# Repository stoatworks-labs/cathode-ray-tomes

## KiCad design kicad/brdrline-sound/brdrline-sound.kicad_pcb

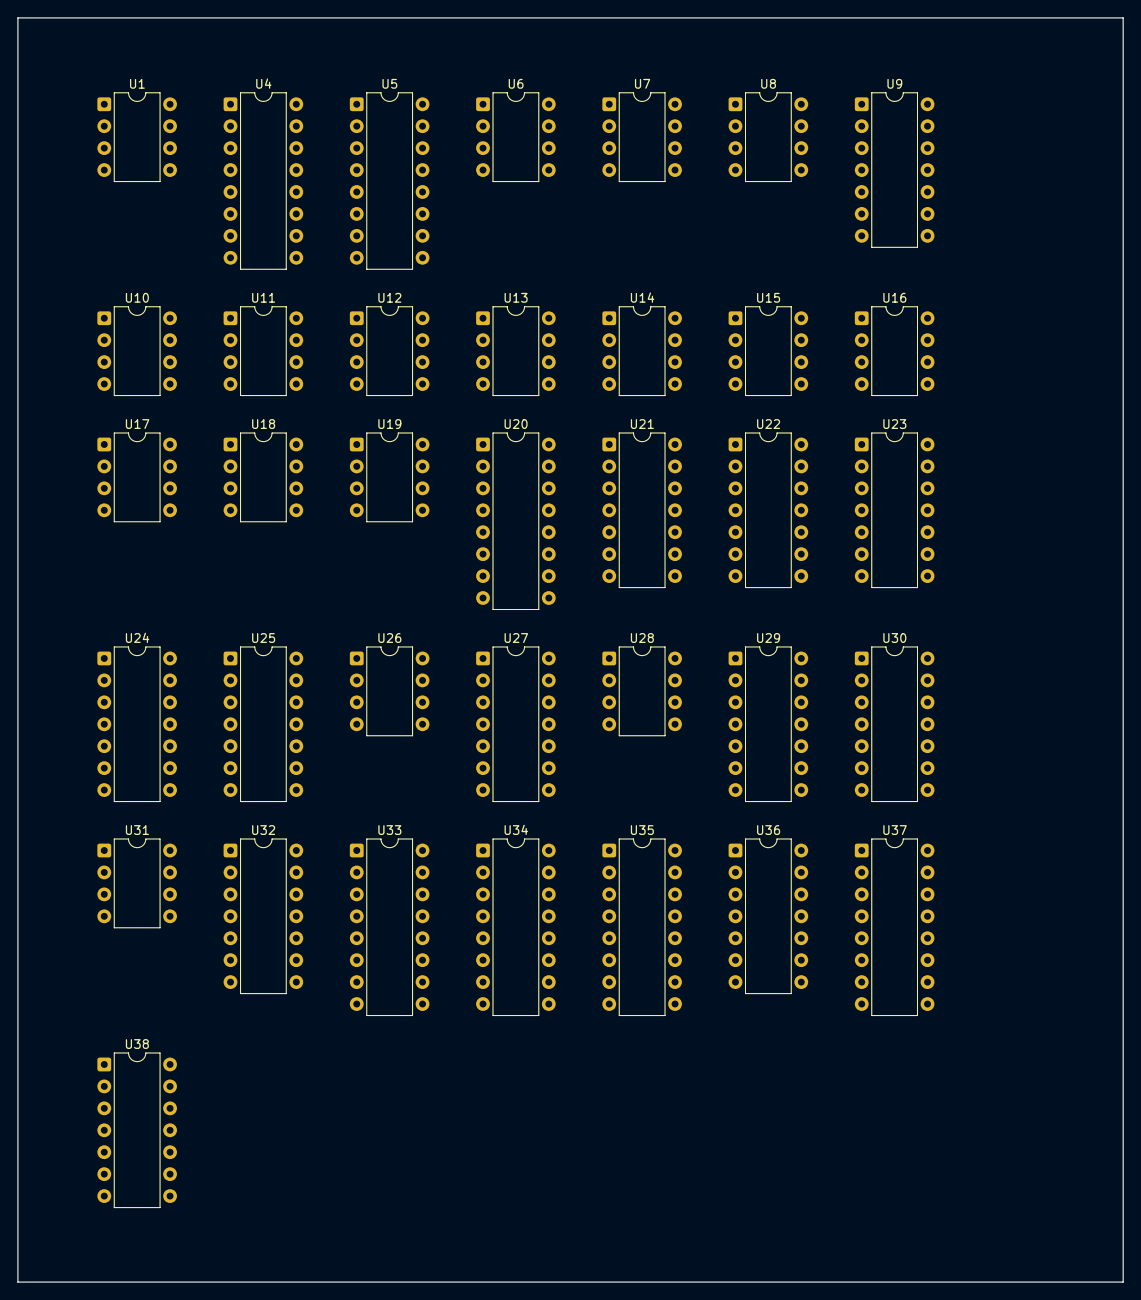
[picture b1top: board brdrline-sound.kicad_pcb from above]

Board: 2 copper layers, 128.0 x 146.4 mm, 36 parts (0 on the bottom side), 39 nets, no tracks yet.

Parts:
U1, U6, U7, U8, U10, U11, U12, U13, U14, U15, U16, U17, U18, U19, U28, U31: NE555; DIP-8_W7.62mm
U4, U5, U20: MB4391; DIP-16_W7.62mm
U9, U21, U22, U23, U24, U25, U27, U38: LM324; DIP-14_W7.62mm
U26: MM5837; DIP-8_W7.62mm
U29: 7408; DIP-14_W7.62mm
U30, U32: 7474; DIP-14_W7.62mm
U33, U34, U35, U37: 74123; DIP-16_W7.62mm
U36: 7416; DIP-14_W7.62mm

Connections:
+5V: U1.8, U4.12, U4.16, U5.12, U5.16, U6.8, U7.8, U8.8, U10.8, U11.8, U12.8, U13.8, U14.8, U15.8, U16.8, U17.8, U18.8, U19.8, U20.12, U20.16, U28.8, U29.14, U30.1, U30.4, U30.10, U30.13, U30.14, U31.8, U32.1, U32.4, U32.10, U32.13, U32.14, U33.2, U33.3, U33.10, U33.11, U33.16, U34.2, U34.3, U34.16, U35.2, U35.3, U35.10, U35.11, U35.16, U36.14, U37.2, U37.3, U37.10, U37.11, U37.16
+6V: U21.5, U27.3, U38.5
+12V: U9.4, U21.4, U22.4, U23.4, U24.4, U25.4, U26.4, U27.4, U38.4
ANIMAL_TRG: U34.1, U34.9
GND: U1.1, U4.3, U4.7, U5.3, U5.7, U6.1, U7.1, U8.1, U9.11, U10.1, U11.1, U12.1, U13.1, U14.1, U15.1, U16.1, U17.1, U18.1, U19.1, U20.3, U20.7, U21.11, U22.11, U23.11, U24.11, U25.11, U26.1, U26.2, U27.11, U28.1, U29.7, U30.7, U31.1, U32.7, U33.8, U34.8, U35.8, U36.7, U37.8, U37.9, U38.11
unnamed: U1.2, U1.6, U9.14
unnamed: U16.2, U16.6, U24.14
unnamed: U10.2, U10.6, U21.14
unnamed: U11.2, U11.6, U21.8
unnamed: U12.2, U12.6, U22.14
unnamed: U13.2, U13.6, U22.8
unnamed: U14.2, U14.6, U23.14
unnamed: U15.2, U15.6, U23.8
unnamed: U17.2, U17.6, U24.8
unnamed: U18.2, U18.6, U25.14
unnamed: U19.2, U19.6, U25.8
unnamed: U6.2, U6.6, U24.1
unnamed: U7.2, U7.6, U25.1
unnamed: U8.2, U8.6, U25.7
unnamed: U31.2, U31.6
unnamed: U28.6, U28.7
unnamed: U9.8, U9.9
unnamed: U18.5, U19.5
unnamed: U34.10, U34.11, U34.13
unnamed: U29.4, U30.8
unnamed: U31.4, U36.6
unnamed: U30.3, U30.11, U31.3, U32.3
unnamed: U32.2, U32.6, U32.11
unnamed: U32.8, U32.12
unnamed: U5.2, U38.13, U38.14
unnamed: U20.2, U27.13, U27.14
unnamed: U20.6, U21.1, U21.2
unnamed: U4.2, U22.6, U22.7
unnamed: U4.6, U23.1, U23.2
unnamed: U29.5, U30.6
unnamed: U29.6, U30.2
unnamed: U30.5, U30.12
unnamed: U5.6, U38.1, U38.2
RST: U1.4, U6.4, U7.4, U8.4, U10.4, U11.4, U12.4, U13.4, U14.4, U15.4, U16.4, U17.4, U18.4, U19.4, U37.12

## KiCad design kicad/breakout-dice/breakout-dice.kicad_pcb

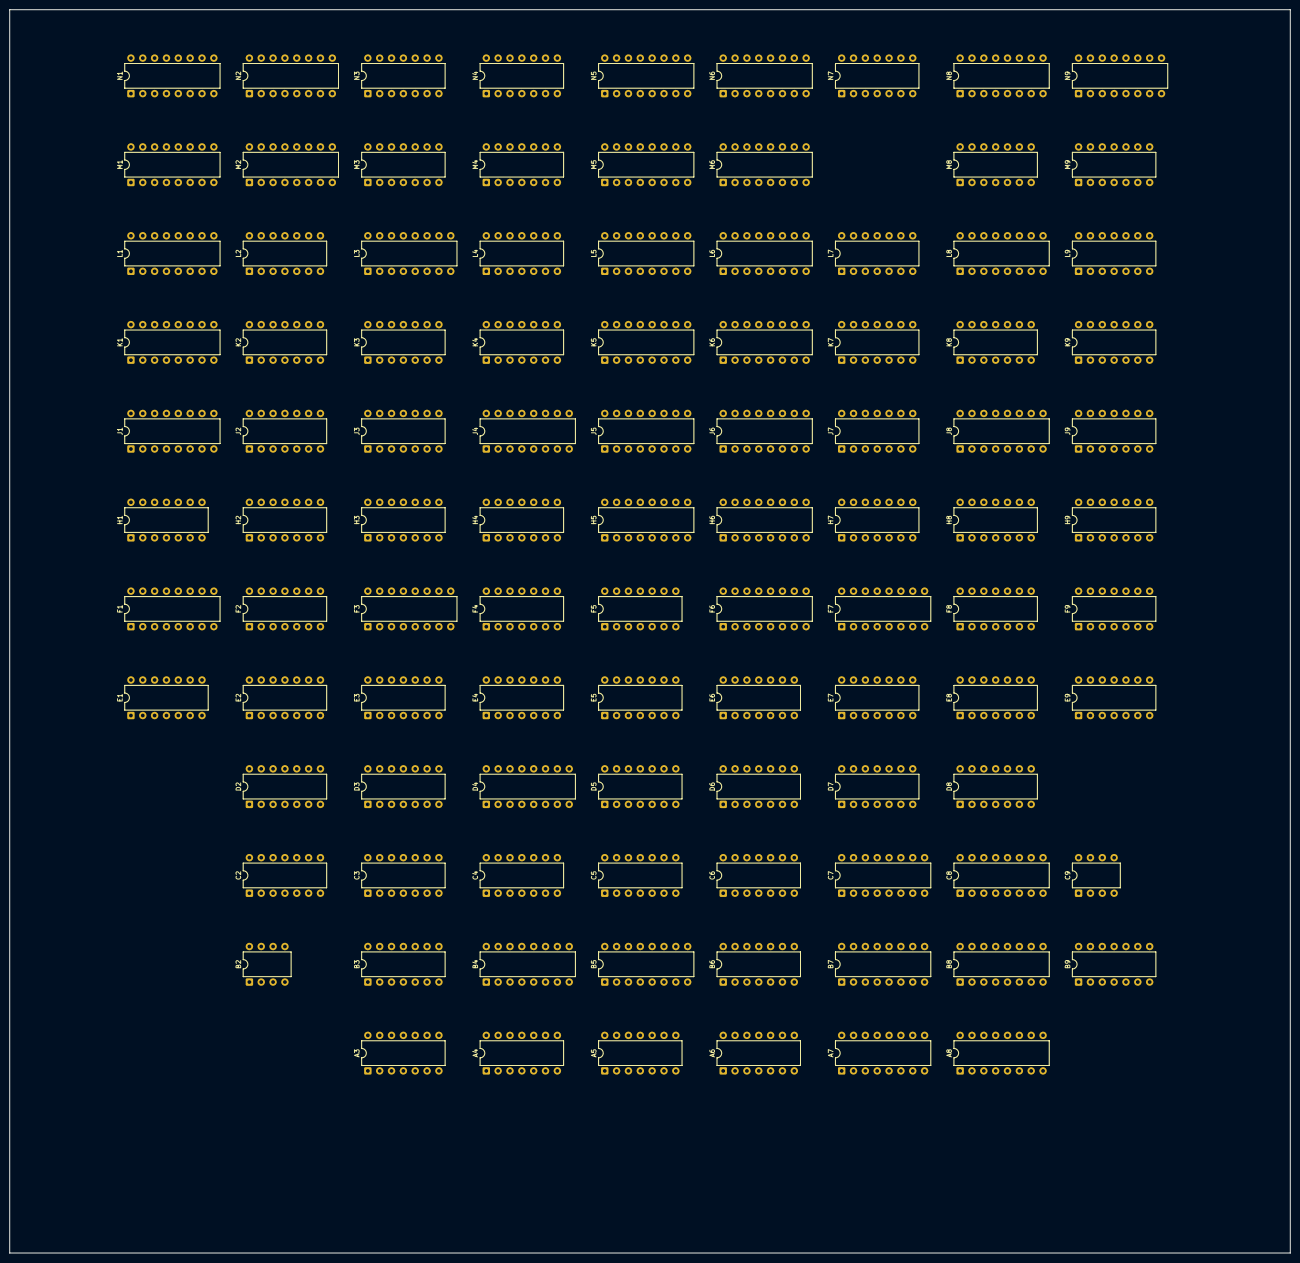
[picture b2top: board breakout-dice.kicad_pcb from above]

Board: 2 copper layers, 274.6 x 266.6 mm, 100 parts (0 on the bottom side), 342 nets, no tracks yet.

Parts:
A3, A6: 7474; DIP-14_W7.62mm
A4: 7408; DIP-14_W7.62mm
A5: 7400; DIP-14_W7.62mm
A7, A8: 9602; DIP-16_W7.62mm
B2: 555; DIP-8_W7.62mm
B3: 7402; DIP-14_W7.62mm
B4, B7, B8: 9316; DIP-16_W7.62mm
B5: 74193; DIP-16_W7.62mm
B6: 7400; DIP-14_W7.62mm
B9: 7408; DIP-14_W7.62mm
C2, C3: 7400; DIP-14_W7.62mm
C4, C6: 7486; DIP-14_W7.62mm
C5: 7404; DIP-14_W7.62mm
C7, C8: 9316; DIP-16_W7.62mm
C9: 555; DIP-8_W7.62mm
D2: 7432; DIP-14_W7.62mm
D3, D5: 7474; DIP-14_W7.62mm
D4: 9316; DIP-16_W7.62mm
D6: 7408; DIP-14_W7.62mm
D7: 7411; DIP-14_W7.62mm
D8: 7400; DIP-14_W7.62mm
E1, E9: 7404; DIP-14_W7.62mm
E2: 7486; DIP-14_W7.62mm
E3, E7: 7402; DIP-14_W7.62mm
E4: 7432; DIP-14_W7.62mm
E5: 7408; DIP-14_W7.62mm
E6, E8: 7474; DIP-14_W7.62mm
F1: 9316; DIP-16_W7.62mm
F2: 7411; DIP-14_W7.62mm
F3: 9602; DIP-16_W7.62mm
F4, F5, F8: 7474; DIP-14_W7.62mm
F6: 74193; DIP-16_W7.62mm
F7: 74279; DIP-16_W7.62mm
F9: 7404; DIP-14_W7.62mm
H1: 7437; DIP-14_W7.62mm
H2, H7: 7408; DIP-14_W7.62mm
H3: 7427; DIP-14_W7.62mm
H4: 7400; DIP-14_W7.62mm
H5: 9312; DIP-16_W7.62mm
H6: 9310; DIP-16_W7.62mm
H8, H9: 7474; DIP-14_W7.62mm
J1: 74175; DIP-16_W7.62mm
J2: 7404; DIP-14_W7.62mm
J3: 7402; DIP-14_W7.62mm
J4: 9312; DIP-16_W7.62mm
J5: 7448; DIP-16_W7.62mm
J6: 9310; DIP-16_W7.62mm
J7: 7420; DIP-14_W7.62mm
J8: 74279; DIP-16_W7.62mm
J9: 7410; DIP-14_W7.62mm
K1: 9316; DIP-16_W7.62mm
K2, K7: 7486; DIP-14_W7.62mm
K3: 7430; DIP-14_W7.62mm
K4: 7408; DIP-14_W7.62mm
K5: 9312; DIP-16_W7.62mm
K6: 9310; DIP-16_W7.62mm
K8: 7474; DIP-14_W7.62mm
K9: 74107; DIP-14_W7.62mm
L1: 9316; DIP-16_W7.62mm
L2, L7: 7486; DIP-14_W7.62mm
L3: 82S16; DIP-16_W7.62mm
L4: 7411; DIP-14_W7.62mm
L5: 9312; DIP-16_W7.62mm
L6: 9310; DIP-16_W7.62mm
L8: 74193; DIP-16_W7.62mm
L9: 7400; DIP-14_W7.62mm
M1: 9316; DIP-16_W7.62mm
M2: 7483; DIP-16_W7.62mm
M3: 7486; DIP-14_W7.62mm
M4: 7410; DIP-14_W7.62mm
M5: 9312; DIP-16_W7.62mm
M6: 9310; DIP-16_W7.62mm
M8: 7427; DIP-14_W7.62mm
M9: 7404; DIP-14_W7.62mm
N1: 9316; DIP-16_W7.62mm
N2: 7483; DIP-16_W7.62mm
N3: 7486; DIP-14_W7.62mm
N4: 7411; DIP-14_W7.62mm
N5: 9312; DIP-16_W7.62mm
N6: 9310; DIP-16_W7.62mm
N7: 7408; DIP-14_W7.62mm
N8: 9602; DIP-16_W7.62mm
N9: 74192; DIP-16_W7.62mm

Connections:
+5V: A3.14, A4.14, A5.14, A6.14, B2.8, B3.14, B4.16, B5.16, B6.14, B7.16, B8.16, B9.14, C2.14, C3.14, C4.14, C5.14, C6.14, C7.16, C8.16, C9.8, D2.14, D3.14, D4.16, D5.14, D6.14, D7.14, D8.14, E1.14, E2.14, E3.14, E4.14, E5.14, E6.14, E7.14, E8.14, E9.14, F1.16, F2.14, F4.14, F5.14, F6.16, F7.16, F8.14, F9.14, H1.14, H2.14, H3.14, H4.14, H5.16, H6.16, H7.14, H8.14, H9.14, J1.16, J2.14, J3.14, J4.16, J5.16, J6.16, J7.14, J8.16, J9.14, K1.16, K2.14, K3.14, K4.14, K5.16, K6.16, K7.14, K8.14, K9.14, L1.16, L2.14, L4.14, L5.16, L6.16, L7.14, L8.16, L9.14, M1.16, M2.5, M3.14, M4.14, M5.16, M6.16, M8.14, M9.14, N1.16, N2.5, N3.14, N4.14, N5.16, N6.16, N7.14, N9.16
A1: H6.14, N5.5
A2: N5.1, N6.14
A3-6: A3.6, B3.9
A3-10: A3.10, A4.8
A3-11: A3.11, L4.12
A3-12: A3.12, B3.13
A4-9: A4.9, C3.6
A4-11: A4.11, C4.9
A5-2: A5.2, A5.13, C5.12
A5-3: A5.3, A5.12, A6.4
A5-11: A5.11, A6.1
A6-5: A6.5, C6.9
A6-8: A6.8, B6.13
A6-12: A6.12, C4.6
A7-6: A7.6, B9.4
A7-9: A7.9, J9.13
A7-11: A7.11, A8.11, F6.4, J9.12
A8-6: A8.6, B9.13
A8-10: A8.10, B9.10
ATTRACT: A3.3, D6.5, E6.8
ATTRACT_n: A7.3, A7.13, A8.3, A8.13, B2.4, C2.13, C3.13, E6.9, E7.3, E7.12, N8.3, N8.13
B1: H6.13, M5.5
B2: M5.1, N6.13
B2-3: B2.3, E9.13
B3-1: B3.1, E7.6
B3-4: B3.4, C3.4
B3-5: B3.5, C3.8
B3-8: B3.8, E1.12
B3-10: B3.10, B3.11
B5-5: B5.5, D6.8
B5-6: B5.6, B6.10, C5.11
B5-7: B5.7, B6.9, C5.9
B6-5: B6.5, C6.8
B6-8: B6.8, D6.9
B7-7: B7.7, B8.10, C8.15
B7-9: B7.9, C7.9, D8.8
B7-10: B7.10, C7.15, C8.7
B7-15: B7.15, B8.7, D8.9
B8-15: B8.15, D7.3, D8.10
BALL: A4.4, D7.6, E1.13
BALL_A: A4.2, A4.13, B4.13, C4.13, C5.5
BALL_B: A4.12, B4.12, C4.12
BALL_C: B4.11, C4.10
BALL_DISPLAY: A4.6, A5.10, C2.1, H2.13, J1.13
BG1_n: J8.11, K8.9
BG2_n: J8.3, K8.5
BONUS_COIN: E7.8, L9.11, N8.4
BP_HIT_n: A5.8, A6.11, A8.5, C5.13, D5.4, E4.2, E4.4, E5.4
BRICK_DISPLAY: E1.1, E3.1
BRICK_HIT: D5.3, E6.5, H2.9, N8.12
BRICK_HIT_n: E6.6, F2.2, F7.10
BRICK_SOUND: B8.14, B9.9
BSYNC: A5.5, C3.2, J1.15
BTB_HIT_n: C3.3, C5.3, E5.1, E5.5
C1: H6.12, L5.5
C2: L5.1, N6.12
C2-2: C2.2, F7.9
C2-3: C2.3, E3.12
C2-4: C2.4, C2.5, H1.6
C2-6: C2.6, C2.9
C2-10: C2.10, J2.8
C2-11: C2.11, H3.10
C3-9: C3.9, H2.11
C3-11: C3.11, D4.7, K3.12
C3-12: C3.12, E4.8
C4-2: C4.2, D5.2, D5.6
C4-8: C4.8, L5.4
C4-11: C4.11, M5.4
C5-4: C5.4, F5.11
C5-6: C5.6, N5.4
C6-2: C6.2, D5.5
C6-4: C6.4, D6.11
C6-12: C6.12, D5.9, D6.12
C7-11: C7.11, C8.10
C7-12: C7.12, D7.10
C7-13: C7.13, D7.11
C9-3: C9.3, H7.5
CKBH: E6.3, F1.13, H1.12
CLOCK: B7.2, B8.2, C7.2, C8.2, H1.11, J1.9, K1.2, L1.2, M1.2, N1.2
COIN: E7.9, L9.6
COUNT: M9.1, N7.4, N7.10, N7.11, N9.4
COUNT_1: H6.2, J6.2, K6.2, N7.8
COUNT_2: L6.2, M6.2, N6.2, N7.6
CREDIT2_n: F7.1, F9.5, L9.2, M8.8
CREDIT_1_OR_2: F9.9, L9.3
CREDIT_1_OR_2_n: D8.13, E7.2, F9.8
CR_START1_n: D8.4, E8.6, F7.6, H7.2
CR_START2: D8.2, E8.9
CR_START2_n: D8.5, E8.8, F7.5
CSW1: F8.4, F8.10, F9.11, F9.12
CSW2: F9.2, F9.3, H9.4, H9.10
CX0: C6.11, C7.3
CX1: C6.6, C7.4
D1: H6.11, K5.5, M4.11
D2: K5.1, M4.1, N6.11
D2-2: D2.2, E3.13, E6.2
D2-3: D2.3, E6.1
D2-6: D2.6, E3.8
D2-9: D2.9, F2.6
D2-10: D2.10, F5.5
D4-2: D4.2, E4.11
D4-15: D4.15, E4.10
D5-1: D5.1, E5.3
D5-11: D5.11, H2.8
D6-3: D6.3, E6.13
D6-6: D6.6, E6.11
D7-5: D7.5, D7.8
D7-12: D7.12, H1.4
D8-3: D8.3, H7.1
DN: C4.3, D6.13
E1: J6.14, N5.6
E1-2: E1.2, H4.1
E1-3: E1.3, H3.8
E1-4: E1.4, L3.13
E1-5: E1.5, F1.15
E1-6: E1.6, F1.9
E2: M6.14, N5.2
E2-6: E2.6, F2.10
E2-8: E2.8, F2.9
E2-13: E2.13, E3.10
E3-2: E3.2, K4.8
E3-3: E3.3, E3.11, L3.6
E4-1: E4.1, M4.12
E4-3: E4.3, F4.3
E4-5: E4.5, M4.8
E4-6: E4.6, F4.11
E4-9: E4.9, H7.6
E4-12: E4.12, E5.11
E4-13: E4.13, E5.8
E5-6: E5.6, F7.11, F7.12
E5-9: E5.9, F5.8
E5-12: E5.12, F5.9
E7-1: E7.1, E8.1
E7-10: E7.10, L8.5
E7-11: E7.11, F7.4
E7-13: E7.13, E8.13
E8-2: E8.2, E9.4
E8-12: E8.12, E9.10
E9-1: E9.1, J3.10
E9-8: E9.8, H1.1, H1.2
EGL: A4.3, C5.1, D8.12, K8.3, K8.11
EGL_n: C5.2, D6.2
F1: J6.13, M5.6
F1-14: F1.14, H1.13
F2: M5.2, M6.13
F2-8: F2.8, H4.4
F2-11: F2.11, H4.11
F2-12: F2.12, L3.12
F3-5: F3.5, F4.6
F3-11: F3.11, F4.8
F6-5: F6.5, F7.15, M9.2
F6-13: F6.13, F7.14
F7-13: F7.13, J9.2
F8-2: F8.2, F8.9
F8-6: F8.6, H8.12
F8-12: F8.12, F9.10
F9-4: F9.4, H9.12
FPD1: F3.10, H3.9
FPD1_n: F2.13, F3.9
FPD2: F3.6, H3.11
FPD2_n: F2.1, F3.7
G1: J6.12, L5.6, M4.10
G2: L5.2, M4.13, M6.12
GND: A3.7, A4.7, A5.7, A6.7, A7.4, A7.12, A8.4, A8.12, B2.1, B3.7, B4.8, B5.8, B6.7, B7.6, B7.8, B8.8, B9.7, C2.7, C3.7, C4.7, C5.7, C6.7, C7.6, C7.8, C8.8, C9.1, D2.7, D3.1, D3.2, D3.3, D3.7, D4.8, D5.7, D6.7, D7.7, D8.7, E1.7, E2.7, E3.7, E4.7, E5.7, E6.7, E7.7, E8.7, E9.7, F1.3, F1.5, F1.6, F1.8, F2.7, F3.4, F3.12, F4.7, F5.7, F6.8, F6.14, F7.8, F8.7, F9.1, F9.7, H1.7, H2.7, H3.7, H4.7, H5.2, H5.3, H5.5, H5.6, H5.8, H5.9, H6.8, H7.7, H8.7, H9.7, J1.8, J2.7, J3.7, J4.3, J4.4, J4.7, J4.8, J4.9, J5.8, J6.8, J7.7, J8.8, J9.7, K1.8, K2.7, K3.7, K4.7, K5.4, K5.8, K5.9, K6.8, K7.7, K8.7, K9.4, K9.7, K9.11, L1.4, L1.6, L1.8, L2.7, L4.7, L5.8, L5.9, L6.8, L7.7, L8.8, L9.7, M1.3, M1.4, M1.6, M1.8, M2.4, M2.11, M2.12, M2.13, M2.16, M3.7, M4.7, M5.8, M6.8, M8.7, M9.7, N1.8, N2.4, N2.11, N2.12, N2.16, N3.7, N4.7, N5.8, N6.8, N7.7, N9.8, N9.9
H01: J6.11, K5.6
H1: F2.3, K4.9, L2.8
H1-10: H1.10, J1.5, N4.6
H1_d: L1.14, L2.9
H2: B3.3, H5.11, K4.10, L2.11, L4.3
H02: K5.2, M6.11
H2-2: H2.2, J2.13, N4.8
H2-4: H2.4, K1.7, L1.15, M1.7
H2-5: H2.5, M1.15
H2-6: H2.6, N1.7
H2_d: L1.13, L2.12
H3-6: H3.6, L4.9
H3-12: H3.12, H4.2
H4: C3.5, H5.12, K3.4, L2.3, L3.2, L4.5
H4-5: H4.5, M8.6
H4-8: H4.8, L3.5
H4-9: H4.9, M4.6
H4-10: H4.10, K4.3
H4-12: H4.12, J4.14
H4-13: H4.13, H5.14
H4_d: L1.12, L2.2
H5-1: H5.1, J5.13
H5-4: H5.4, J5.14
H5-7: H5.7, J5.10
H5-10: H5.10, K4.11
H6-15: H6.15, J6.10
H7-3: H7.3, L8.4
H8: H5.13, J2.1, J3.2, J4.11, L2.6, L3.1, L4.4, L4.11
H8-2: H8.2, H9.6
H8-5: H8.5, J8.6, J9.5
H8-9: H8.9, J8.15, J9.9
H8_d: B3.6, L1.11, L2.5
H8_n: J2.2, N9.1
H9-2: H9.2, H9.9
H16: E2.9, J2.5, K2.8, K3.11, L3.15, L4.1, L4.10
H16_d: K1.14, K2.9
H16_n: H2.10, J2.6, N9.10
H32: H3.3, J2.3, J3.3, J3.5, J5.5, K2.11, L3.3
H32_d: K1.13, K2.12
H32_n: J2.4, K5.10, L5.10, M5.10, N5.10
H64: E5.13, H3.5, J3.6, J3.8, K2.3, K3.6, K4.1
H64_d: K1.12, K2.2
H128: E5.10, F5.1, H2.12, H3.4, J3.9, K2.6, K3.5, L3.4, L4.2
H128_d: K1.11, K2.5
HSYNC: C3.10, J1.2
HSYNC_n: E2.12, J1.3, K9.10, K9.13
I1: K6.14, K7.2, N5.7
I2: L6.14, L7.2, N5.3
J1: K6.13, K7.12, M5.7
J2: L6.13, L7.12, M5.3
J2-12: J2.12, J3.11
J3-1: J3.1, K3.1
J3-4: J3.4, L4.13
J4-1: J4.1, J5.12
J4-2: J4.2, J5.11
J4-5: J4.5, J5.15
J4-6: J4.6, J5.9
J4-10: J4.10, L4.6
J5-1: J5.1, M5.15
J5-2: J5.2, L5.15
J5-6: J5.6, K5.15
J5-7: J5.7, N5.15
J6-15: J6.15, K6.10
J7-1: J7.1, L7.3
J7-2: J7.2, L7.11
J7-4: J7.4, L7.6
J7-5: J7.5, L7.8
J7-6: J7.6, J8.1
J7-8: J7.8, J8.10
J7-9: J7.9, K7.8
J7-10: J7.10, K7.6
J7-12: J7.12, K7.11
J7-13: J7.13, K7.3
J8-4: J8.4, K8.2, K9.12
J8-7: J8.7, J9.4
J8-9: J8.9, K8.12, K9.9
J8-13: J8.13, J9.10
J9-6: J9.6, L9.4
J9-8: J9.8, L9.5
K1: K6.12, K7.5, L5.7, M4.9
K2: L5.3, L6.12, L7.5, M4.2
K4-5: K4.5, L4.8
K7-1: K7.1, L7.1
K7-4: K7.4, L7.4
K7-10: K7.10, L7.10
K7-13: K7.13, L7.13
K9-2: K9.2, L9.13
K9-6: K9.6, L9.12
L1: K5.7, K6.11, K7.9
L2: K5.3, L6.11, L7.9
L6-10: L6.10, M6.15
L8-2: L8.2, M8.11
L8-3: L8.3, M9.13
L8-6: L8.6, M8.10
L8-7: L8.7, M8.9
L8-11: L8.11, L8.12
L8-13: L8.13, L9.9
L8-14: L8.14, L9.8
L9-1: L9.1, M9.12
LH_SIDE: H3.1, J3.13
M2-2: M2.2, M3.5
M2-6: M2.6, M3.2
M2-14: M2.14, N2.13
M2-15: M2.15, M3.12
M3-8: M3.8, M8.2
M6-10: M6.10, N6.15
M8-3: M8.3, M8.12
N2-2: N2.2, N3.5
N2-6: N2.6, N3.2
N2-9: N2.9, N3.9
N2-15: N2.15, N3.12
N4-11: N4.11, N4.12
N7-1: N7.1, N8.6
N7-13: N7.13, N9.13
N8-9: N8.9, N9.11
P2_CONDITIONAL: C4.1, C6.1, H1.3, K2.1, K2.4, K2.10, K2.13, L2.1, L2.4, L2.10, L2.13, M2.7, M3.1, M3.4, M3.13, N2.7, N3.1, N3.4, N3.10, N3.13
P2_CONDITIONAL_dash: E9.9, H7.8
PAD_EN_n: C2.8, C9.2, C9.4, H7.4
PAD_n: J1.12, K3.8
PC: C4.4, D4.12
PD: A5.1, C4.5, D4.11
PLAYER_2: B4.14, E7.5, F2.4, H7.10, L6.7, M5.9, M6.7, M9.9, N6.7, N7.5
PLAYER_2_n: M3.9, M9.8, N5.9
PLAY_CP: B4.2, D2.8
PLGM2_n: F2.5, F7.7
PLNR: E2.10, E3.4, M8.13
PSYNC: A5.9, B9.1, J1.11
P_HIT_SOUND: B7.12, B9.12, D7.4
Q: D6.1, E9.6, K8.4, K8.10, L9.10
RAM_PLAYER1: E7.4, H6.7, J6.7, K6.7, L3.11, N7.9
RH_SIDE: H2.3, H3.2
SBD_n: D2.11, E5.2
SCI_n: D3.4, H4.6
SCLOCK: J1.4, K1.15, M1.10, N7.12
SERVE_WAIT: A3.1, A3.9, B5.14, F5.3
SERVE_WAIT_n: A3.8, A4.5, B3.12, D2.13, D5.13, F5.13
SERVE_n: A3.4, D2.12, D3.13
SET_BRICKS: D2.1, D3.9
SET_BRICKS_n: B3.2, C2.12, D3.8, E6.4
SFL_n: E9.12, M8.1
START_GAME: D3.11, D8.6, E6.12, M9.3, M9.5, N9.14
START_GAME1_n: A4.10, B4.1, F4.1, F4.13, J8.2, J8.12, M9.4
START_GAME_n: F6.11, H6.1, J6.1, K6.1, L6.1, M6.1, M9.6, N6.1
SU_n: B5.11, D5.8
TOP_BOUND: C3.1, H3.13, K4.6
TOP_n: E9.2, M8.4, M8.5
V1_d: M1.14, M2.10
V2: M3.3, M4.5
V2_d: M1.13, M2.8
V4: J4.12, K4.12, M3.6, M4.4, N4.9
V4_d: M1.12, M2.3, N7.2
V8: D8.1, J4.13, K4.13, M3.11, M4.3, N4.10
V8_d: D2.5, H1.5, M1.11, M2.1
V16: J2.11, K5.11, L3.10, L5.11, M5.11, N3.8, N4.13, N5.11
V16_d: A6.2, D2.4, D7.1, H8.3, H8.11, J8.5, J8.14, N1.14, N2.10
V16_n: E3.6, J2.10
V32: D6.4, E2.4, E3.5, H2.1, J3.12, L3.14, N3.3
V32_d: J2.9, N1.13, N2.8, N4.4
V64: E2.5, H7.12, H7.13, K5.12, L3.7, L5.12, M5.12, M9.11, N3.6, N4.2, N5.12
V64I: E8.11, F8.3, F8.11, H7.11
V64_d: D7.13, E8.3, N1.12, N2.3, N4.3
V64_n: H9.3, H9.11, M9.10
V128: K5.13, L3.9, L5.13, M3.10, M5.13, N3.11, N4.1, N5.13
V128_d: D7.2, F7.2, F7.3, N1.11, N2.1, N4.5
VB_HIT_SOUND: B7.11, B9.5, D7.9
VB_HIT_n: A5.6, A6.3, A7.5
VCC: A3.2, A3.13, A6.10, A6.13, B4.7, B4.9, B4.10, B5.1, B5.4, B5.9, B5.10, B5.15, B7.1, B8.1, B8.3, B8.4, B8.5, B8.6, B8.9, C7.1, C7.7, C7.10, C8.1, C8.3, C8.4, C8.5, C8.6, C8.9, D3.10, D3.12, D4.3, D4.4, D4.5, D4.6, D4.9, D4.10, D5.10, D5.12, E6.10, E8.4, E8.10, F1.1, F1.4, F1.7, F1.10, F3.3, F3.13, F4.2, F4.4, F4.10, F4.12, F5.2, F5.4, F5.10, F5.12, F6.1, F6.9, F6.10, F6.15, F8.1, F8.13, H6.9, H6.10, H8.1, H8.4, H8.10, H8.13, H9.1, H9.13, J1.1, J5.3, J5.4, J6.9, J9.3, K1.1, K1.3, K1.4, K1.5, K1.6, K1.9, K1.10, K3.2, K3.3, K6.9, K8.1, K8.13, K9.1, K9.8, L1.1, L1.3, L1.5, L1.7, L1.10, L6.9, L8.1, L8.9, L8.10, L8.15, M1.1, M1.5, M6.9, N1.1, N1.3, N1.4, N1.5, N1.6, N1.9, N1.10, N6.9, N6.10, N8.5, N8.11, N9.5, N9.15
VERT_TRIG_n: H1.8, L1.9, M1.9
VSYNC: A5.4, J1.7, J9.1
VSYNC_n: B9.2, D4.1, E3.9, H1.9, J1.6, K4.2, K4.4
V_SLOW: B6.12, C5.8, C6.10
X0: B6.1, C5.10, C6.13
X1: B6.3, C6.5
X2: B6.2, C6.3, C7.5, D6.10
Y0: B6.4, B6.11, B7.3
Y1: B6.6, B7.4
Y2: A6.6, B7.5
